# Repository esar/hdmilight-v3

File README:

This is a still-in-progress update to my hdmilight-v2 project.

Differences in this version:
 * Everything is on a standalone board, no longer needs a Papilio FPGA board
 * AVR CPU removed from FPGA design and replaced by a separate ARM Cortex MCU.
   The main reason for this change was to get more program memory. The FPGA
   had no more spare block RAMs. It also has the advantage of being a much
   more capable CPU and having live debugging via JTAG.
 * Power supply switching for the LEDs. This version can power down the 
   LED strips when not in use.
 * Extra pins added to each LED output port, now have +5V, DAT, GND, CLK
   Currently it still only support 3-wire LED strips, but in the future
   it should be able to support 4-wire clocked strips
 * Magical mystery connectors (vivepos / papix). The real reason I made
   this revision... a platform to experiment with my crazy ideas

Build instructions:

 1) Manufacture the HDMI receiver board that can be found in 
    the 'board' directory (KiCad format).
 2) Open the 'fpga/hdmilight.xise' project in Xilinx ISE and
    generate a bit file.
 3) Edit the files under the config directory to configure
    the LEDs.
 5) Run 'make' in the top level directory, which will do the following:
      * Build the firmware image
      * Convert the text config file to binary format
      * Append the config to the end of the FPGA bit file
      * Flash the ARM microcontroller with the firmware
      * Flash the FPGA config flash with the bit file
 8) Connect LED strips to output pins
 9) Open a serial terminal to the board 
    (running "dmesg" is useful to see names of recently added serial ports)
 10) Connect HDMI source to receiver board
 11) It should now be working. 

This version should now have feature parity with version 2, however
it has not been tested very well yet.

Useful build targets:
 * make firmware: build the firmware without flashing
 * make firmware_flash: flash the last build to the ARM
 * make fpga_program: reprogram FPGA without programming flash
                      will be lost on thxt power-cycle
 * make fpga_flash: reprogram the FPGA flash
 * make fpga_flash_config: reprogram just the configuration part of the FPGA flash

Debugging the firmware:
 1) start openocd: openocd -f hdmilight-v3-openocd.cfg
 2) start gdb: arm-none-eabi-gdb
 3) in gdb, load firmware: file firmware/main.elf
 4) in gdb, connect to board: target remote :3333

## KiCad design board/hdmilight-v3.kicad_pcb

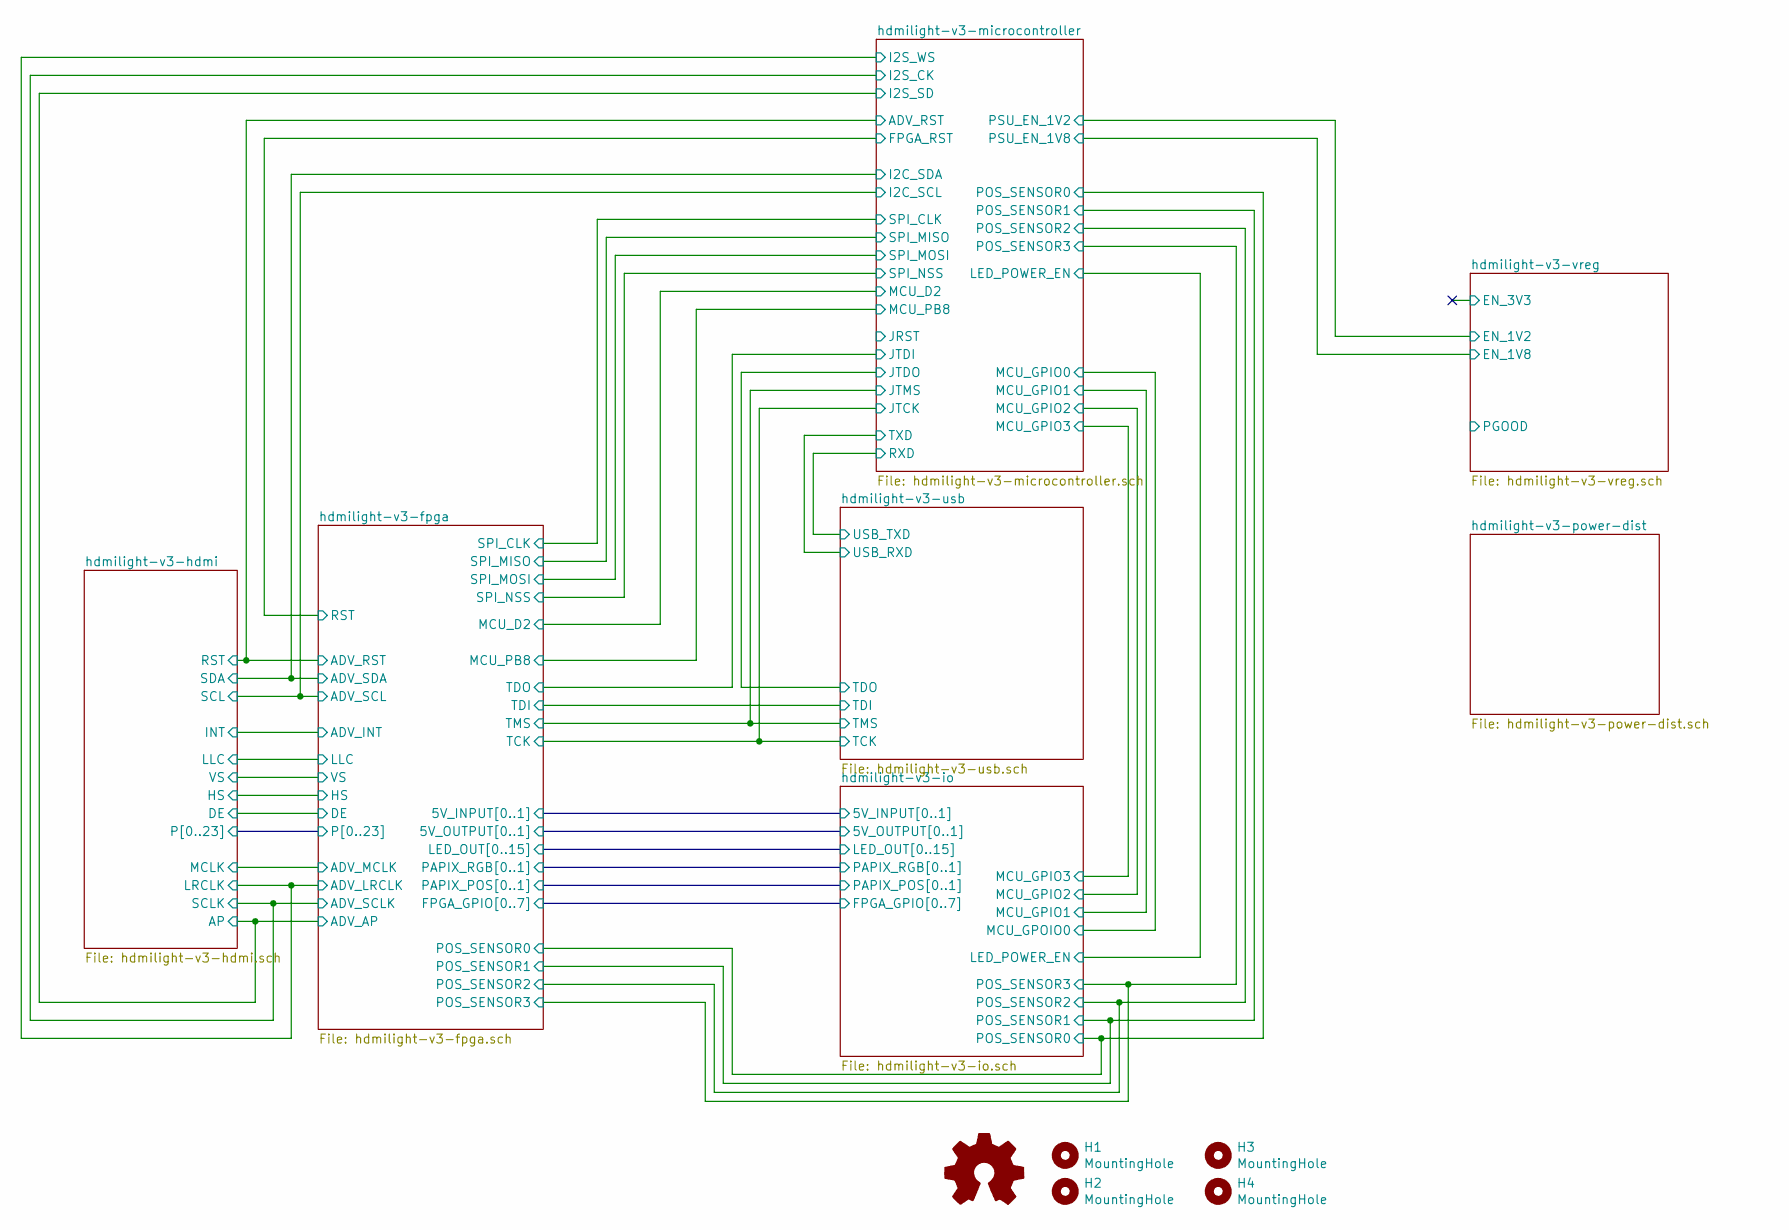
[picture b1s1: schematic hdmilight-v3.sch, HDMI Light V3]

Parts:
H1, H2, H3, H4: MountingHole; MountingHole_3.2mm_M3
LOGO1: Logo_Open_Hardware_Small; OSHW-Logo2_9.8x8mm_SilkScreen

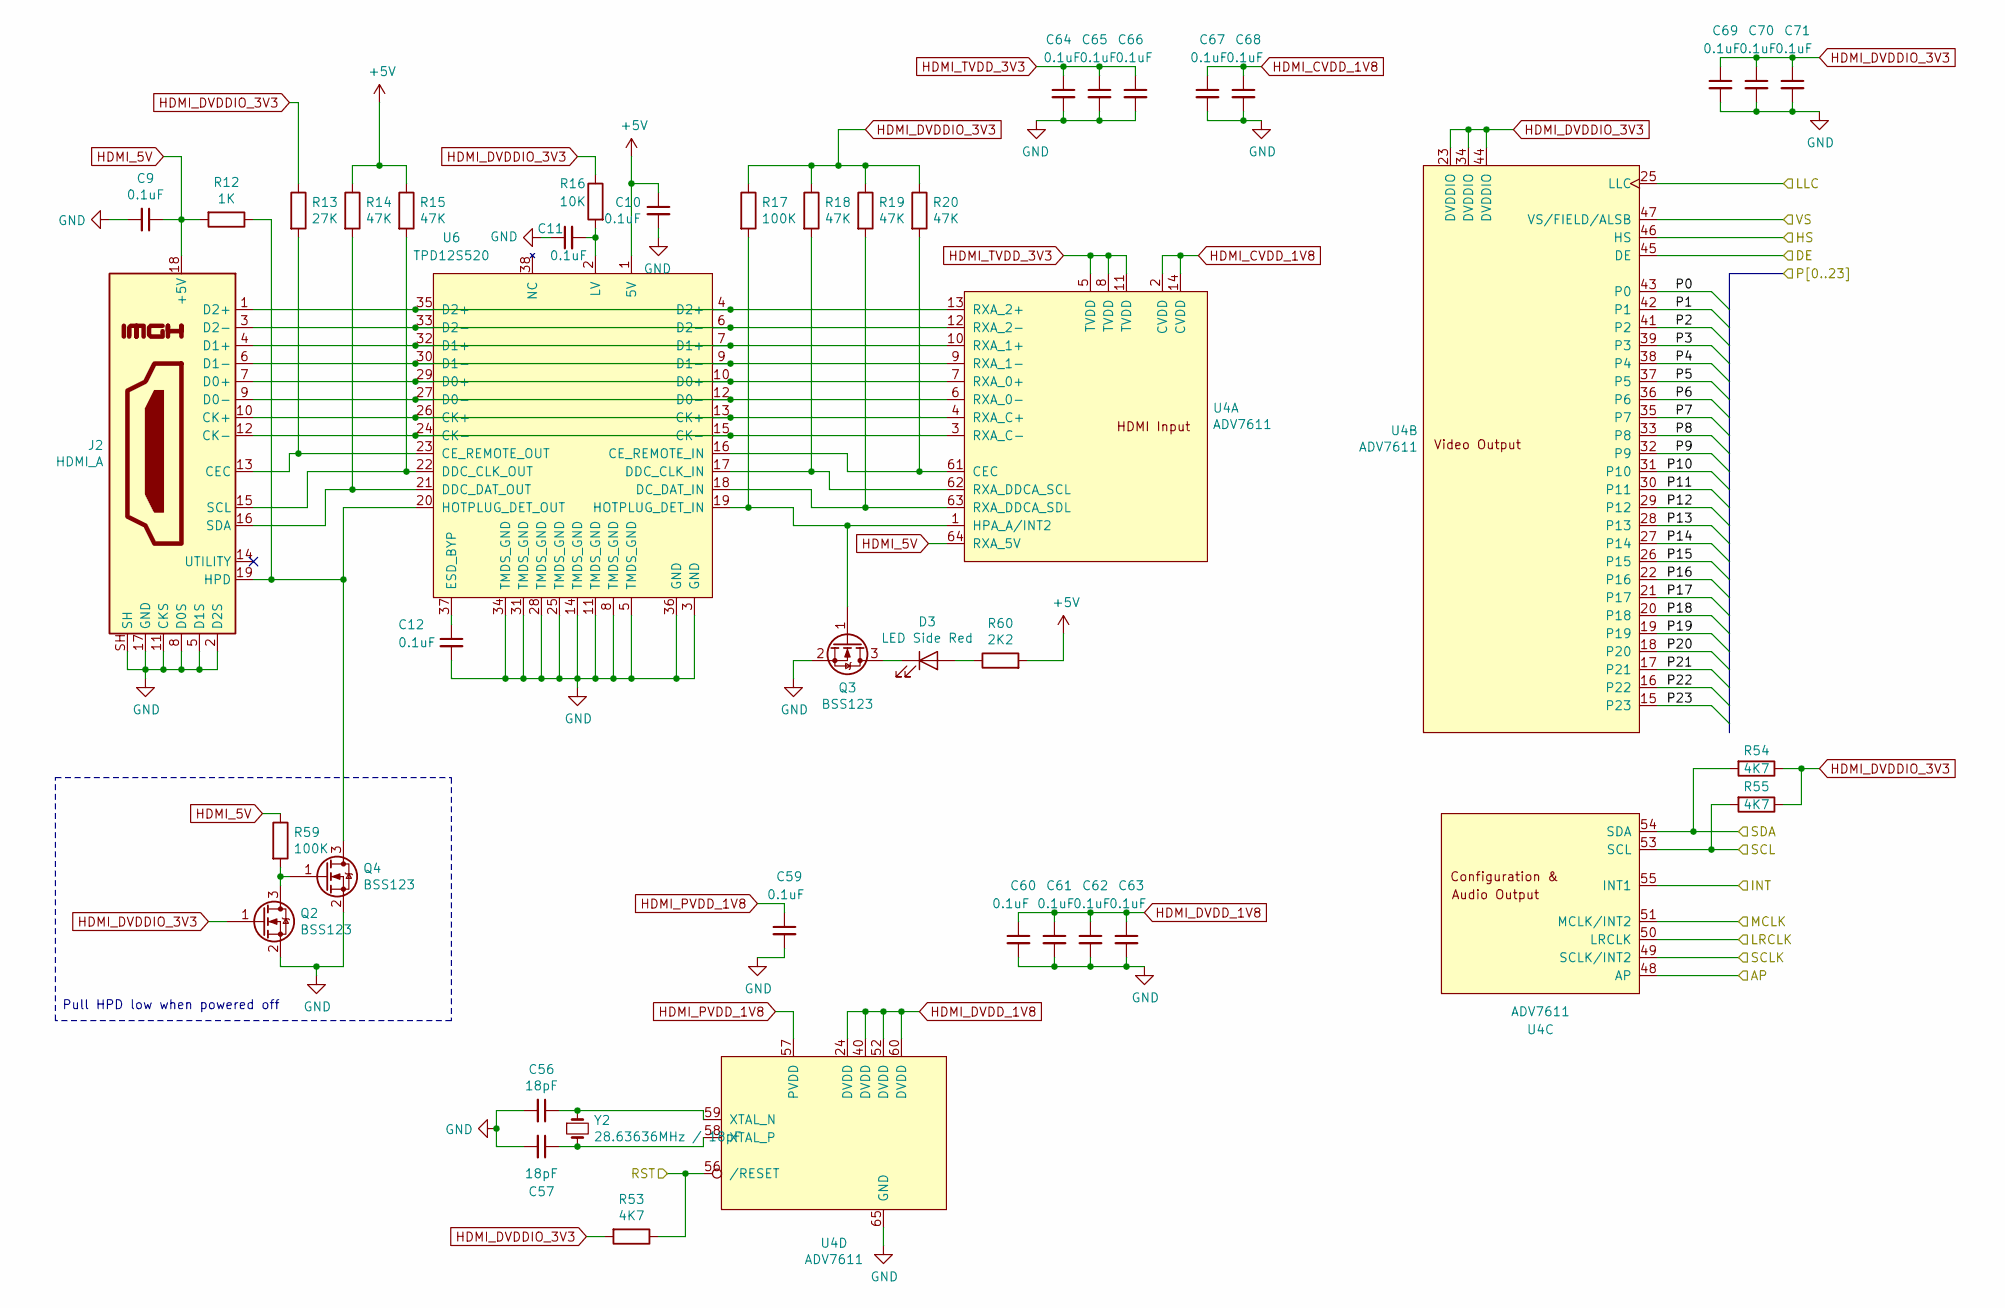
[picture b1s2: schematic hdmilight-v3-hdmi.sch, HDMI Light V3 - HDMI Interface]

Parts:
C9, C59, C60, C61, C62, C63, C64, C65, C66, C67, C68, C69, C70, C71: 0.1uF; C_0402_1005Metric
C10, C11, C12: 0.1uF; C_0603_1608Metric
C56, C57: 18pF; C_0603_1608Metric
D3: LED Side Red; LED_0603_1608Metric
J2: HDMI_A; HDMI_SOCKET_FCI_10029449
Q2, Q3, Q4: BSS123; SOT-23
R12: 1K; R_0603_1608Metric
R13: 27K; R_0603_1608Metric
R14, R15, R18, R19, R20: 47K; R_0603_1608Metric
R16: 10K; R_0603_1608Metric
R17, R59: 100K; R_0603_1608Metric
R53, R54, R55: 4K7; R_0603_1608Metric
R60: 2K2; R_0603_1608Metric
U4: ADV7611; LQFP-64-1EP_10x10mm_P0.5mm_EP6.5x6.5mm_ThermalVias
U6: TPD12S520; TSSOP-38_4.4x9.7mm_P0.5mm
Y2: 28.63636MHz / 18pF; Crystal_SMD_5032-2Pin_5.0x3.2mm

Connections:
+5V: C10.1, R14.1, R15.1, R60.2, U6.1 (5V); also elsewhere on the board
/hdmilight-v3-fpga/ADV_AP: U4.48 (AP); also elsewhere on the board
/hdmilight-v3-fpga/ADV_INT: U4.55 (INT1); also elsewhere on the board
/hdmilight-v3-fpga/ADV_LRCLK: U4.50 (LRCLK); also elsewhere on the board
/hdmilight-v3-fpga/ADV_MCLK: U4.51 (MCLK/INT2); also elsewhere on the board
/hdmilight-v3-fpga/ADV_RST: R53.1, U4.56 (/RESET); also elsewhere on the board
/hdmilight-v3-fpga/ADV_SCL: R55.2, U4.53 (SCL); also elsewhere on the board
/hdmilight-v3-fpga/ADV_SCLK: U4.49 (SCLK/INT2); also elsewhere on the board
/hdmilight-v3-fpga/ADV_SDA: R54.2, U4.54 (SDA); also elsewhere on the board
/hdmilight-v3-fpga/DE: U4.45 (DE); also elsewhere on the board
/hdmilight-v3-fpga/HS: U4.46 (HS); also elsewhere on the board
/hdmilight-v3-fpga/LLC: U4.25 (LLC); also elsewhere on the board
/hdmilight-v3-fpga/P0: U4.43 (P0); also elsewhere on the board
/hdmilight-v3-fpga/P1: U4.42 (P1); also elsewhere on the board
/hdmilight-v3-fpga/P2: U4.41 (P2); also elsewhere on the board
/hdmilight-v3-fpga/P3: U4.39 (P3); also elsewhere on the board
/hdmilight-v3-fpga/P4: U4.38 (P4); also elsewhere on the board
/hdmilight-v3-fpga/P5: U4.37 (P5); also elsewhere on the board
/hdmilight-v3-fpga/P6: U4.36 (P6); also elsewhere on the board
/hdmilight-v3-fpga/P7: U4.35 (P7); also elsewhere on the board
/hdmilight-v3-fpga/P8: U4.33 (P8); also elsewhere on the board
/hdmilight-v3-fpga/P9: U4.32 (P9); also elsewhere on the board
/hdmilight-v3-fpga/P10: U4.31 (P10); also elsewhere on the board
/hdmilight-v3-fpga/P11: U4.30 (P11); also elsewhere on the board
/hdmilight-v3-fpga/P12: U4.29 (P12); also elsewhere on the board
/hdmilight-v3-fpga/P13: U4.28 (P13); also elsewhere on the board
/hdmilight-v3-fpga/P14: U4.27 (P14); also elsewhere on the board
/hdmilight-v3-fpga/P15: U4.26 (P15); also elsewhere on the board
/hdmilight-v3-fpga/P16: U4.22 (P16); also elsewhere on the board
/hdmilight-v3-fpga/P17: U4.21 (P17); also elsewhere on the board
/hdmilight-v3-fpga/P18: U4.20 (P18); also elsewhere on the board
/hdmilight-v3-fpga/P19: U4.19; also elsewhere on the board
/hdmilight-v3-fpga/P20: U4.18 (P20); also elsewhere on the board
/hdmilight-v3-fpga/P21: U4.17 (P21); also elsewhere on the board
/hdmilight-v3-fpga/P22: U4.16 (P22); also elsewhere on the board
/hdmilight-v3-fpga/P23: U4.15 (P23); also elsewhere on the board
/hdmilight-v3-fpga/VS: U4.47 (VS/FIELD/ALSB); also elsewhere on the board
GND: C9.2, C10.2, C11.1, C12.2, C56.2, C57.2, C59.2, C60.2, C61.2, C62.2, C63.2, C64.2, C65.2, C66.2, C67.2, C68.2, C69.2, C70.2, C71.2, J2.2 (D2S), J2.5 (D1S), J2.8 (D0S), J2.11 (CKS), J2.17 (GND), J2.SH, Q2.2 (S), Q3.2 (S), Q4.2 (S), U4.65 (GND), U6.3 (GND), U6.5 (TMDS_GND), U6.8 (TMDS_GND), U6.11 (TMDS_GND), U6.14 (TMDS_GND), U6.25 (TMDS_GND), U6.28 (TMDS_GND), U6.31 (TMDS_GND), U6.34 (TMDS_GND), U6.36 (GND); also elsewhere on the board
HDMI_5V: C9.1, J2.18 (+5V), R12.2, R59.1, U4.64 (RXA_5V)
HDMI_CVDD_1V8: C67.1, C68.1, U4.2 (CVDD), U4.14 (CVDD); also elsewhere on the board
HDMI_DVDDIO_3V3: C69.1, C70.1, C71.1, Q2.1 (G), R13.1, R16.1, R17.1, R18.1, R19.1, R20.1, R53.2, R54.1, R55.1, U4.23 (DVDDIO), U4.34 (DVDDIO), U4.44 (DVDDIO); also elsewhere on the board
HDMI_DVDD_1V8: C60.1, C61.1, C62.1, C63.1, U4.24 (DVDD), U4.40 (DVDD), U4.52 (DVDD), U4.60 (DVDD); also elsewhere on the board
HDMI_PVDD_1V8: C59.1, U4.57 (PVDD); also elsewhere on the board
HDMI_TVDD_3V3: C64.1, C65.1, C66.1, U4.5 (TVDD), U4.8 (TVDD), U4.11 (TVDD); also elsewhere on the board
unnamed: C11.2, R16.2, U6.2 (LV)
unnamed: C12.1, U6.37 (ESD_BYP)
unnamed: C56.1, U4.59 (XTAL_N), Y2.1
unnamed: C57.1, U4.58 (XTAL_P), Y2.2
unnamed: D3.1 (K), Q3.3 (D)
unnamed: D3.2 (A), R60.1
unnamed: J2.1 (D2+), U4.13 (RXA_2+), U6.4 (D2+), U6.35 (D2+)
unnamed: J2.3 (D2-), U4.12 (RXA_2-), U6.6 (D2-), U6.33 (D2-)
unnamed: J2.4 (D1+), U4.10 (RXA_1+), U6.7 (D1+), U6.32 (D1+)
unnamed: J2.6 (D1-), U4.9 (RXA_1-), U6.9 (D1-), U6.30 (D1-)
unnamed: J2.7 (D0+), U4.7 (RXA_0+), U6.10 (D0+), U6.29 (D0+)
unnamed: J2.9 (D0-), U4.6 (RXA_0-), U6.12 (D0-), U6.27 (D0-)
unnamed: J2.10 (CK+), U4.4 (RXA_C+), U6.13 (CK+), U6.26 (CK+)
unnamed: J2.12 (CK-), U4.3 (RXA_C-), U6.15 (CK-), U6.24 (CK-)
unnamed: J2.13 (CEC), R13.2, U6.23 (CE_REMOTE_OUT)
unnamed: J2.15 (SCL), R15.2, U6.22 (DDC_CLK_OUT)
unnamed: J2.16 (SDA), R14.2, U6.21 (DDC_DAT_OUT)
unnamed: J2.19 (HPD), Q4.3 (D), R12.1, U6.20 (HOTPLUG_DET_OUT)
unnamed: Q2.3 (D), Q4.1 (G), R59.2
unnamed: Q3.1 (G), R17.2, U4.1 (HPA_A/INT2), U6.19 (HOTPLUG_DET_IN)
unnamed: R18.2, U4.62 (RXA_DDCA_SCL), U6.17 (DDC_CLK_IN)
unnamed: R19.2, U4.63 (RXA_DDCA_SDL), U6.18 (DC_DAT_IN)
unnamed: R20.2, U4.61 (CEC), U6.16 (CE_REMOTE_IN)

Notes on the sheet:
Pull HPD low when powered off

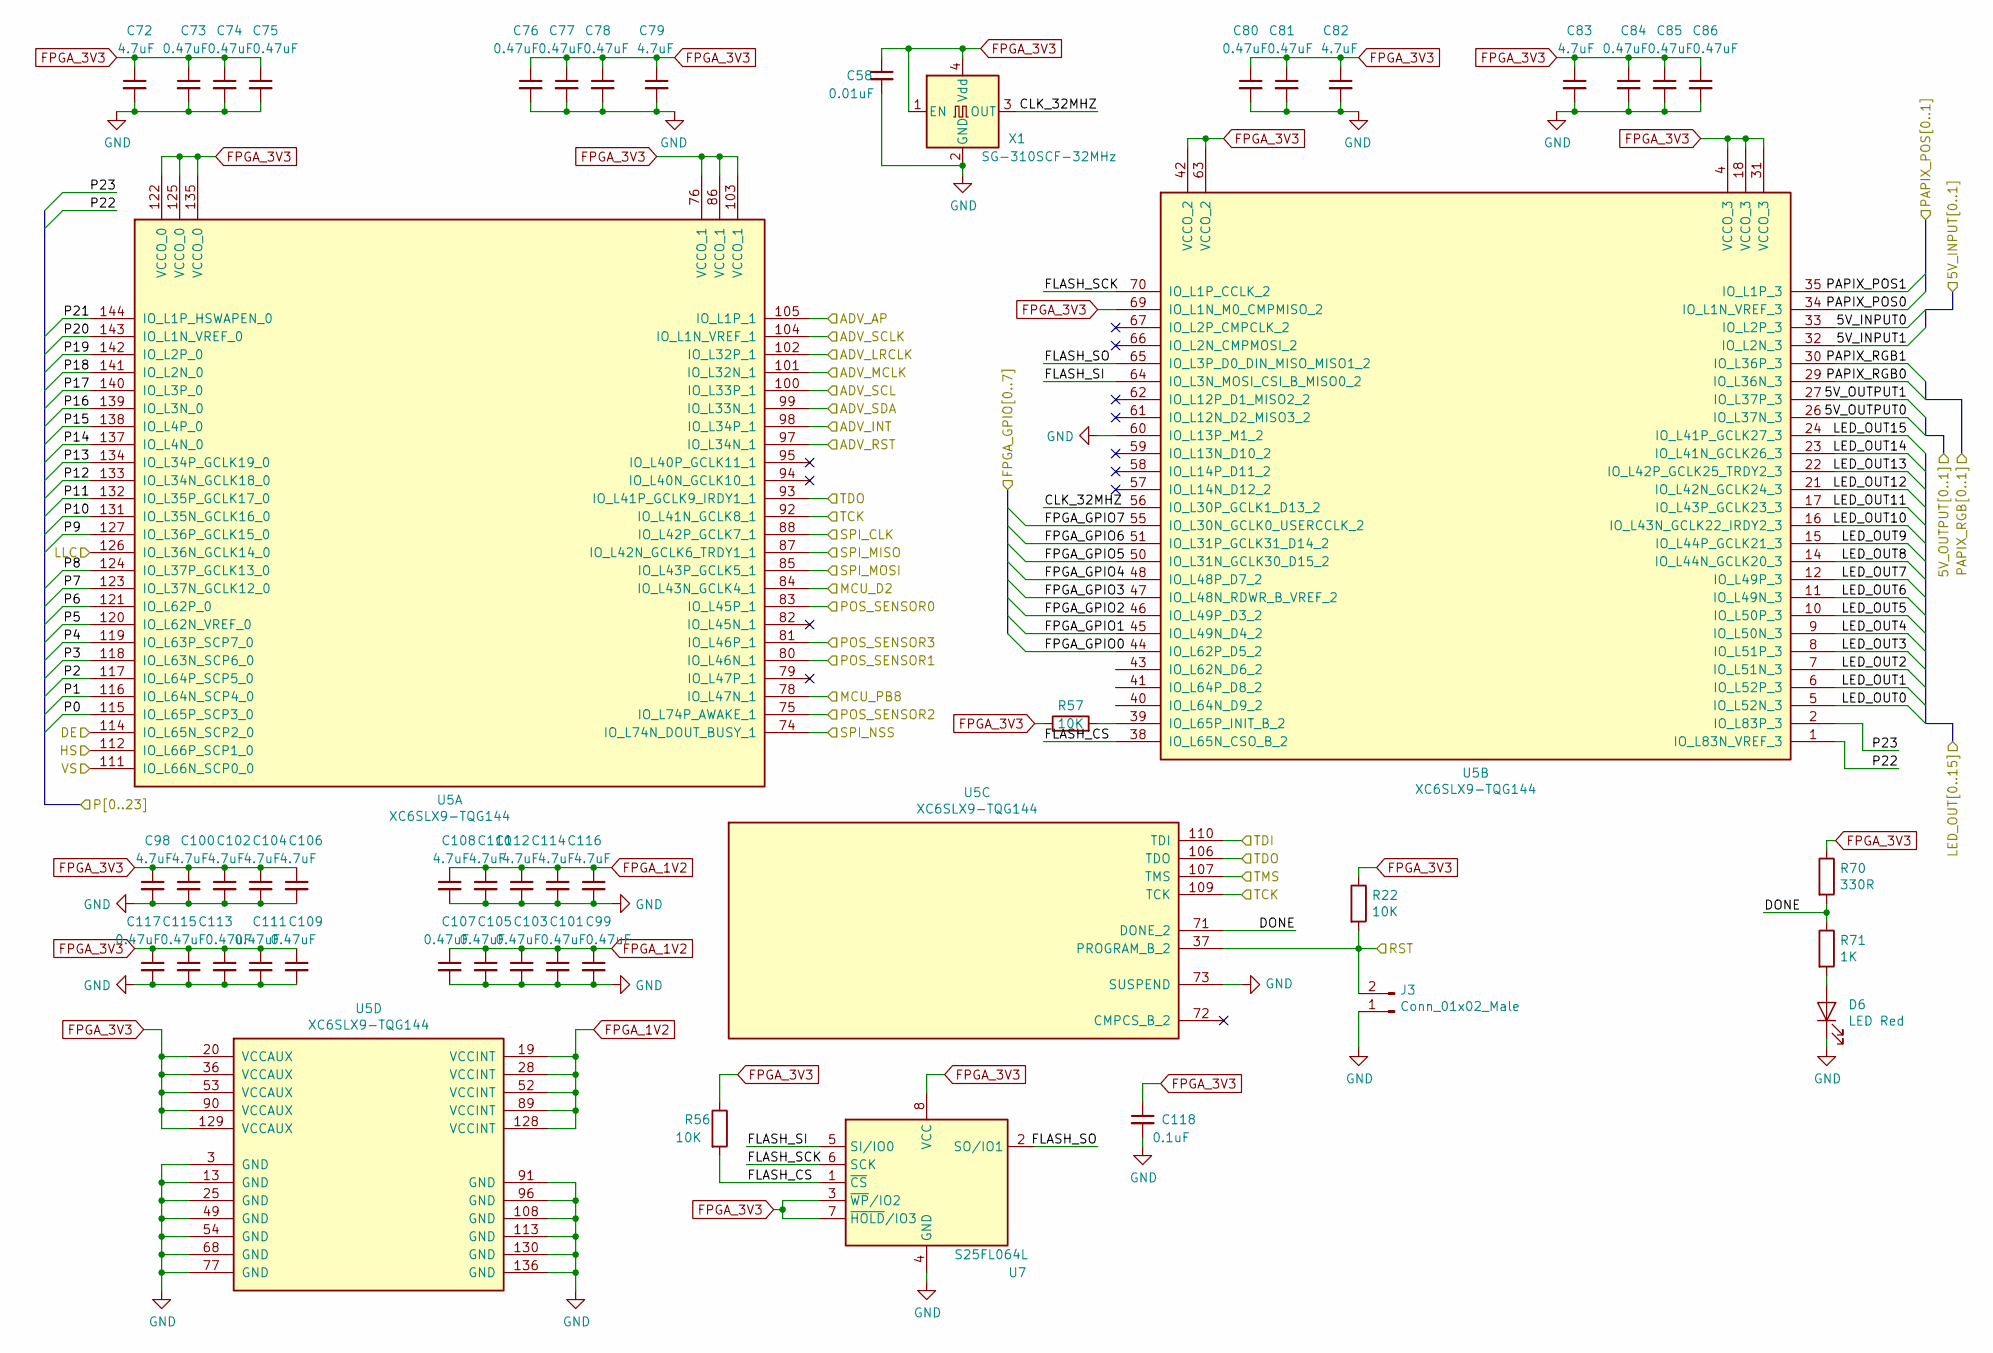
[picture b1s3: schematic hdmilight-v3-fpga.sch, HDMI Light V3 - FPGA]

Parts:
C58: 0.01uF; C_0603_1608Metric
C72, C79, C82, C83, C98, C100, C102, C104, C106, C108, C110, C112, C114, C116: 4.7uF; C_0805_2012Metric
C73, C74, C75, C76, C77, C78, C80, C81, C84, C85, C86, C99, C101, C103, C105, C107, C109, C111, C113, C115, C117: 0.47uF; C_0402_1005Metric
C118: 0.1uF; C_0402_1005Metric
D6: LED Red; LED_0603_1608Metric
J3: Conn_01x02_Male; PinHeader_1x02_P2.54mm_Vertical
R22, R56, R57: 10K; R_0603_1608Metric
R70: 330R; R_0603_1608Metric
R71: 1K; R_0603_1608Metric
U5: XC6SLX9-TQG144; TQFP-144_20x20mm_P0.5mm
U7: S25FL064L; SOIC-8_5.23x5.23mm_P1.27mm
X1: SG-310SCF-32MHz; Oscillator_SMD_Abracon_ASE-4Pin_3.2x2.5mm

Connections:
/hdmilight-v3-fpga/5V_INPUT0: U5.33 (IO_L2P_3); also elsewhere on the board
/hdmilight-v3-fpga/5V_INPUT1: U5.32 (IO_L2N_3); also elsewhere on the board
/hdmilight-v3-fpga/5V_OUTPUT0: U5.26 (IO_L37N_3); also elsewhere on the board
/hdmilight-v3-fpga/5V_OUTPUT1: U5.27 (IO_L37P_3); also elsewhere on the board
/hdmilight-v3-fpga/ADV_AP: U5.105 (IO_L1P_1); also elsewhere on the board
/hdmilight-v3-fpga/ADV_INT: U5.98 (IO_L34P_1); also elsewhere on the board
/hdmilight-v3-fpga/ADV_LRCLK: U5.102 (IO_L32P_1); also elsewhere on the board
/hdmilight-v3-fpga/ADV_MCLK: U5.101 (IO_L32N_1); also elsewhere on the board
/hdmilight-v3-fpga/ADV_RST: U5.97 (IO_L34N_1); also elsewhere on the board
/hdmilight-v3-fpga/ADV_SCL: U5.100 (IO_L33P_1); also elsewhere on the board
/hdmilight-v3-fpga/ADV_SCLK: U5.104 (IO_L1N_VREF_1); also elsewhere on the board
/hdmilight-v3-fpga/ADV_SDA: U5.99 (IO_L33N_1); also elsewhere on the board
/hdmilight-v3-fpga/CLK_32MHZ: U5.56 (IO_L30P_GCLK1_D13_2), X1.3 (OUT)
/hdmilight-v3-fpga/DE: U5.114 (IO_L65N_SCP2_0); also elsewhere on the board
/hdmilight-v3-fpga/DONE: R70.2, R71.1, U5.71 (DONE_2)
/hdmilight-v3-fpga/FLASH_CS: R56.2, U5.38 (IO_L65N_CSO_B_2), U7.1 (~CS)
/hdmilight-v3-fpga/FLASH_SCK: U5.70 (IO_L1P_CCLK_2), U7.6 (SCK)
/hdmilight-v3-fpga/FLASH_SI: U5.64 (IO_L3N_MOSI_CSI_B_MISO0_2), U7.5 (SI/IO0)
/hdmilight-v3-fpga/FLASH_SO: U5.65 (IO_L3P_D0_DIN_MISO_MISO1_2), U7.2 (SO/IO1)
/hdmilight-v3-fpga/FPGA_GPIO0: U5.44 (IO_L62P_D5_2); also elsewhere on the board
/hdmilight-v3-fpga/FPGA_GPIO1: U5.45 (IO_L49N_D4_2); also elsewhere on the board
/hdmilight-v3-fpga/FPGA_GPIO2: U5.46 (IO_L49P_D3_2); also elsewhere on the board
/hdmilight-v3-fpga/FPGA_GPIO3: U5.47 (IO_L48N_RDWR_B_VREF_2); also elsewhere on the board
/hdmilight-v3-fpga/FPGA_GPIO4: U5.48 (IO_L48P_D7_2); also elsewhere on the board
/hdmilight-v3-fpga/FPGA_GPIO5: U5.50 (IO_L31N_GCLK30_D15_2); also elsewhere on the board
/hdmilight-v3-fpga/FPGA_GPIO6: U5.51 (IO_L31P_GCLK31_D14_2); also elsewhere on the board
/hdmilight-v3-fpga/FPGA_GPIO7: U5.55 (IO_L30N_GCLK0_USERCCLK_2); also elsewhere on the board
/hdmilight-v3-fpga/HS: U5.112 (IO_L66P_SCP1_0); also elsewhere on the board
/hdmilight-v3-fpga/LED_OUT0: U5.5 (IO_L52N_3); also elsewhere on the board
/hdmilight-v3-fpga/LED_OUT1: U5.6 (IO_L52P_3); also elsewhere on the board
/hdmilight-v3-fpga/LED_OUT2: U5.7 (IO_L51N_3); also elsewhere on the board
/hdmilight-v3-fpga/LED_OUT3: U5.8 (IO_L51P_3); also elsewhere on the board
/hdmilight-v3-fpga/LED_OUT4: U5.9 (IO_L50N_3); also elsewhere on the board
/hdmilight-v3-fpga/LED_OUT5: U5.10 (IO_L50P_3); also elsewhere on the board
/hdmilight-v3-fpga/LED_OUT6: U5.11 (IO_L49N_3); also elsewhere on the board
/hdmilight-v3-fpga/LED_OUT7: U5.12 (IO_L49P_3); also elsewhere on the board
/hdmilight-v3-fpga/LED_OUT8: U5.14 (IO_L44N_GCLK20_3); also elsewhere on the board
/hdmilight-v3-fpga/LED_OUT9: U5.15 (IO_L44P_GCLK21_3); also elsewhere on the board
/hdmilight-v3-fpga/LED_OUT10: U5.16 (IO_L43N_GCLK22_IRDY2_3); also elsewhere on the board
/hdmilight-v3-fpga/LED_OUT11: U5.17 (IO_L43P_GCLK23_3); also elsewhere on the board
/hdmilight-v3-fpga/LED_OUT12: U5.21 (IO_L42N_GCLK24_3); also elsewhere on the board
/hdmilight-v3-fpga/LED_OUT13: U5.22 (IO_L42P_GCLK25_TRDY2_3); also elsewhere on the board
/hdmilight-v3-fpga/LED_OUT14: U5.23 (IO_L41N_GCLK26_3); also elsewhere on the board
/hdmilight-v3-fpga/LED_OUT15: U5.24 (IO_L41P_GCLK27_3); also elsewhere on the board
/hdmilight-v3-fpga/LLC: U5.126 (IO_L36N_GCLK14_0); also elsewhere on the board
/hdmilight-v3-fpga/MCU_D2: U5.84 (IO_L43N_GCLK4_1); also elsewhere on the board
/hdmilight-v3-fpga/MCU_PB8: U5.78 (IO_L47N_1); also elsewhere on the board
/hdmilight-v3-fpga/P0: U5.115 (IO_L65P_SCP3_0); also elsewhere on the board
/hdmilight-v3-fpga/P1: U5.116 (IO_L64N_SCP4_0); also elsewhere on the board
/hdmilight-v3-fpga/P2: U5.117 (IO_L64P_SCP5_0); also elsewhere on the board
/hdmilight-v3-fpga/P3: U5.118 (IO_L63N_SCP6_0); also elsewhere on the board
/hdmilight-v3-fpga/P4: U5.119 (IO_L63P_SCP7_0); also elsewhere on the board
/hdmilight-v3-fpga/P5: U5.120 (IO_L62N_VREF_0); also elsewhere on the board
/hdmilight-v3-fpga/P6: U5.121 (IO_L62P_0); also elsewhere on the board
/hdmilight-v3-fpga/P7: U5.123 (IO_L37N_GCLK12_0); also elsewhere on the board
/hdmilight-v3-fpga/P8: U5.124 (IO_L37P_GCLK13_0); also elsewhere on the board
/hdmilight-v3-fpga/P9: U5.127 (IO_L36P_GCLK15_0); also elsewhere on the board
/hdmilight-v3-fpga/P10: U5.131 (IO_L35N_GCLK16_0); also elsewhere on the board
/hdmilight-v3-fpga/P11: U5.132 (IO_L35P_GCLK17_0); also elsewhere on the board
/hdmilight-v3-fpga/P12: U5.133 (IO_L34N_GCLK18_0); also elsewhere on the board
/hdmilight-v3-fpga/P13: U5.134 (IO_L34P_GCLK19_0); also elsewhere on the board
/hdmilight-v3-fpga/P14: U5.137 (IO_L4N_0); also elsewhere on the board
/hdmilight-v3-fpga/P15: U5.138 (IO_L4P_0); also elsewhere on the board
/hdmilight-v3-fpga/P16: U5.139 (IO_L3N_0); also elsewhere on the board
/hdmilight-v3-fpga/P17: U5.140 (IO_L3P_0); also elsewhere on the board
/hdmilight-v3-fpga/P18: U5.141 (IO_L2N_0); also elsewhere on the board
/hdmilight-v3-fpga/P19: U5.142 (IO_L2P_0); also elsewhere on the board
/hdmilight-v3-fpga/P20: U5.143 (IO_L1N_VREF_0); also elsewhere on the board
/hdmilight-v3-fpga/P21: U5.144 (IO_L1P_HSWAPEN_0); also elsewhere on the board
/hdmilight-v3-fpga/P22: U5.1 (IO_L83N_VREF_3); also elsewhere on the board
/hdmilight-v3-fpga/P23: U5.2 (IO_L83P_3); also elsewhere on the board
/hdmilight-v3-fpga/PAPIX_POS0: U5.34 (IO_L1N_VREF_3); also elsewhere on the board
/hdmilight-v3-fpga/PAPIX_POS1: U5.35 (IO_L1P_3); also elsewhere on the board
/hdmilight-v3-fpga/PAPIX_RGB0: U5.29 (IO_L36N_3); also elsewhere on the board
/hdmilight-v3-fpga/PAPIX_RGB1: U5.30 (IO_L36P_3); also elsewhere on the board
/hdmilight-v3-fpga/POS_SENSOR0: U5.83 (IO_L45P_1); also elsewhere on the board
/hdmilight-v3-fpga/POS_SENSOR1: U5.80 (IO_L46N_1); also elsewhere on the board
/hdmilight-v3-fpga/POS_SENSOR2: U5.75 (IO_L74P_AWAKE_1); also elsewhere on the board
/hdmilight-v3-fpga/POS_SENSOR3: U5.81 (IO_L46P_1); also elsewhere on the board
/hdmilight-v3-fpga/SPI_CLK: U5.88 (IO_L42P_GCLK7_1); also elsewhere on the board
/hdmilight-v3-fpga/SPI_MISO: U5.87 (IO_L42N_GCLK6_TRDY1_1); also elsewhere on the board
/hdmilight-v3-fpga/SPI_MOSI: U5.85 (IO_L43P_GCLK5_1); also elsewhere on the board
/hdmilight-v3-fpga/SPI_NSS: U5.74 (IO_L74N_DOUT_BUSY_1); also elsewhere on the board
/hdmilight-v3-fpga/TDI: U5.110 (TDI); also elsewhere on the board
/hdmilight-v3-fpga/VS: U5.111 (IO_L66N_SCP0_0); also elsewhere on the board
/hdmilight-v3-microcontroller/FPGA_RST: J3.2, R22.2, U5.37 (PROGRAM_B_2); also elsewhere on the board
/hdmilight-v3-microcontroller/JTCK: U5.92 (IO_L41N_GCLK8_1), U5.109 (TCK); also elsewhere on the board
/hdmilight-v3-microcontroller/JTDI: U5.93 (IO_L41P_GCLK9_IRDY1_1), U5.106 (TDO); also elsewhere on the board
/hdmilight-v3-microcontroller/JTMS: U5.107 (TMS); also elsewhere on the board
FPGA_1V2: C99.1, C101.1, C103.1, C105.1, C107.1, C108.1, C110.1, C112.1, C114.1, C116.1, U5.19 (VCCINT), U5.28 (VCCINT), U5.52 (VCCINT), U5.89 (VCCINT), U5.128 (VCCINT); also elsewhere on the board
FPGA_3V3: C58.1, C72.1, C73.1, C74.1, C75.1, C76.1, C77.1, C78.1, C79.1, C80.1, C81.1, C82.1, C83.1, C84.1, C85.1, C86.1, C98.1, C100.1, C102.1, C104.1, C106.1, C109.1, C111.1, C113.1, C115.1, C117.1, C118.1, R22.1, R56.1, R57.1, R70.1, U5.4 (VCCO_3), U5.18 (VCCO_3), U5.20 (VCCAUX), U5.31 (VCCO_3), U5.36 (VCCAUX), U5.42 (VCCO_2), U5.53 (VCCAUX), U5.63 (VCCO_2), U5.69 (IO_L1N_M0_CMPMISO_2), U5.76 (VCCO_1), U5.86 (VCCO_1), U5.90 (VCCAUX), U5.103 (VCCO_1), U5.122 (VCCO_0), U5.125 (VCCO_0), U5.129 (VCCAUX), U5.135 (VCCO_0), U7.3 (~WP~/IO2), U7.7 (~HOLD~/IO3), U7.8 (VCC), X1.1 (EN), X1.4 (Vdd); also elsewhere on the board
GND: C58.2, C72.2, C73.2, C74.2, C75.2, C76.2, C77.2, C78.2, C79.2, C80.2, C81.2, C82.2, C83.2, C84.2, C85.2, C86.2, C98.2, C99.2, C100.2, C101.2, C102.2, C103.2, C104.2, C105.2, C106.2, C107.2, C108.2, C109.2, C110.2, C111.2, C112.2, C113.2, C114.2, C115.2, C116.2, C117.2, C118.2, D6.1 (K), J3.1, U5.3 (GND), U5.13 (GND), U5.25 (GND), U5.49 (GND), U5.54 (GND), U5.60 (IO_L13P_M1_2), U5.68 (GND), U5.73 (SUSPEND), U5.77 (GND), U5.91 (GND), U5.96 (GND), U5.108 (GND), U5.113 (GND), U5.130 (GND), U5.136 (GND), U7.4 (GND), X1.2 (GND); also elsewhere on the board
unnamed: D6.2 (A), R71.2
unnamed: R57.2, U5.39 (IO_L65P_INIT_B_2)

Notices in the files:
board/hdmilight-v3.kicad_pcb:
(c) 2020
